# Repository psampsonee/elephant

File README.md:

# Elephant

This project is intended to be a low-power audio player for a stuffed animal. The goal is to make a box that goes into a stuffed animal that takes up minimal space and lasts as long as possible on a single battery. The box should make an animal noise when its shaken, but only after some time has elapsed since the last time it has made a noise. The noise should be audible in a quiet room and should be immediately recognizable as a particular animal - in this case, an elephant. When the box has just been shaken, it will count - with very little power - a certain amount of time, then after that, wait to be shaken. Then, if you don't shake it, it should sit there, sipping very little power. When you do, it should make the animal noise within some amount of time (maybe a few fractions of a second).

## Power Budget / Battery Life

The board will have three main power states, corresponding to the three states of the state machine:

- Low-power
    - In this state, the STM32 is in standby mode. Everything but the backup domain - that is, the RTC and the backup registers - is powered off. Due to the quiescent currents of various devices during this state, it is expected that a little under 1 uA of current will draw from the main batteries.
- Buck Converter Off
    - The STM32 backup domain is powered only from its VBAT pin by the CR-2032 coin cell. Only the RTC and the backup registers are powered. This allows the STM32 to retain an accurate representation of the time. This will draw up to 2 uA from the CR-2032. However, testing will need to be done to verify this current consumption with the RTC in its particular configuration.
    - In this state, the buck converter becomes the predominate power sink for the main batteries, drawing 1 uA of current while shut down.
- Play Sound (highest power)
    - The microcontroller and DAC/amplifier (SSM2518) are both active, and the SSM2518 draws most of the current. This state will last for a few seconds, but contributes to a significant amount of the energy consumption of the main batteries. The LT-8640 will be supplying roughly 3.7W in this state and drawing 0.41A from the battery.

## State Machine

This firmware uses the Gang-of-Four State pattern: Elephant is the Context and each concrete state implements enter/toggle/exit. Each state is exposed via a singleton instance (no per-state heap allocations); any per-device data lives in the Elephant object. Interrupt service routines are kept tiny — they set flags or enqueue events — and the main loop/state handlers process those events and perform transitions, ensuring deterministic, non-blocking behavior. See notes in the README about concurrency (brief critical sections) and buffer sizing (samples vs bytes) (TODO).

The states in the state machine will correspond to each of the states mentioned in the **Power Budget / Battery Life** section above, with the following transition causes and tasks:

- Light Sleep
    - Upon waking up from standby, the firmware will detect why was reset (confirm entering standby), and why it woke (confirm RTC alarm) in main(). Once the STM32 is in this state, the STM32 will be in standby mode, corresponding to the "Low-power" power state.
    - Transitions to Deep Sleep when real time clock alarm fires. When the alarm fires, the STM32 briefly powers on completely to do the transition. During this transition, the microcontroller must save any data that needs to be retained (probably: last sound played (avoid repetition) and any state information needing to be retained) to spare backup registers, then pull the *GPIO_pwr_buck_off* pin low, triggering the 74AUP1G74 to clear, tying the LT8640 EN/UV pin low and causing it to power down.
- Deep Sleep
    - This state never sees a transition to another state in the code as the STM32 is completely powered off during it. Instead, the transition from this state occurs when the STM32 powers back on due to the LT8640 restoring power to the board. Corresponds to **Buck Converter Off**
    - "Transitions" to Play Sound when the tilt switch pulls the preload pin of the 74AUP1G74 low briefly, pulling Q high and turning the LT8640 back on.
- Play Sound
    - Upon powering on, the firmware will detect why was reset (POR), and why it woke (power restored) in main().  In this state, the STM32 will prepare the EEPROM for reading, then load data from the EEPROM in packets while playing a sound through the Audio object. Corresponds to the power state of the same name.
    - Transitions to Light Sleep when the Audio object completes playing a sound. During this transition, the STM32 sets an alarm 4 hours ahead of the current time to trigger it to wake up and transition into deep sleep.

## Choice of Components

### LT8640 Buck Converter

The LT8640 was chosen due to its high efficiency and ability to be turned off via the enable pin, which takes very little current to drive and allows the battery to be **practically** disconnected from the circuit (x nA is expected to leak while the LT8640 is turned off).

### STM32F401CCU Microcontroller

- Powerful enough to play intelligible audio
- Low-power options allow for RTC battery backup and external wakeups
- Nearly the same chip as on a "Black Pill" (For development)

### M95M04 EEPROM

- 4 Mbit is enough for several audio files (show calcs)
- Low Power
- 200 year data retention - not an SD card

### SSM2518 I2S DAC and amplifier

- Low quiescent current
- A one-chip solution to audio (maybe I dont need to say this in the final readme)
- Powerful enough to be heard at 2W per channel
-Very low noise

### LM66100 ideal diodes (power source OR-ing)

- Low quiescent (0.3uA) and leakage (max 600nA at operating temperature) currents
- Actively controlled PFET limits reverse-current to nanoamps. This is especially important for the coin cell to avoid damage, especially in high-temperature environments where a BAT54 could cause a failure in low-power mode.
- LM66100 ideal diodes were selected for power-source OR-ing due to their low quiescent current and low reverse leakage; reverse-current behavior into the coin cell is still being validated in simulation.

## Next Steps

## Risks and Unknowns

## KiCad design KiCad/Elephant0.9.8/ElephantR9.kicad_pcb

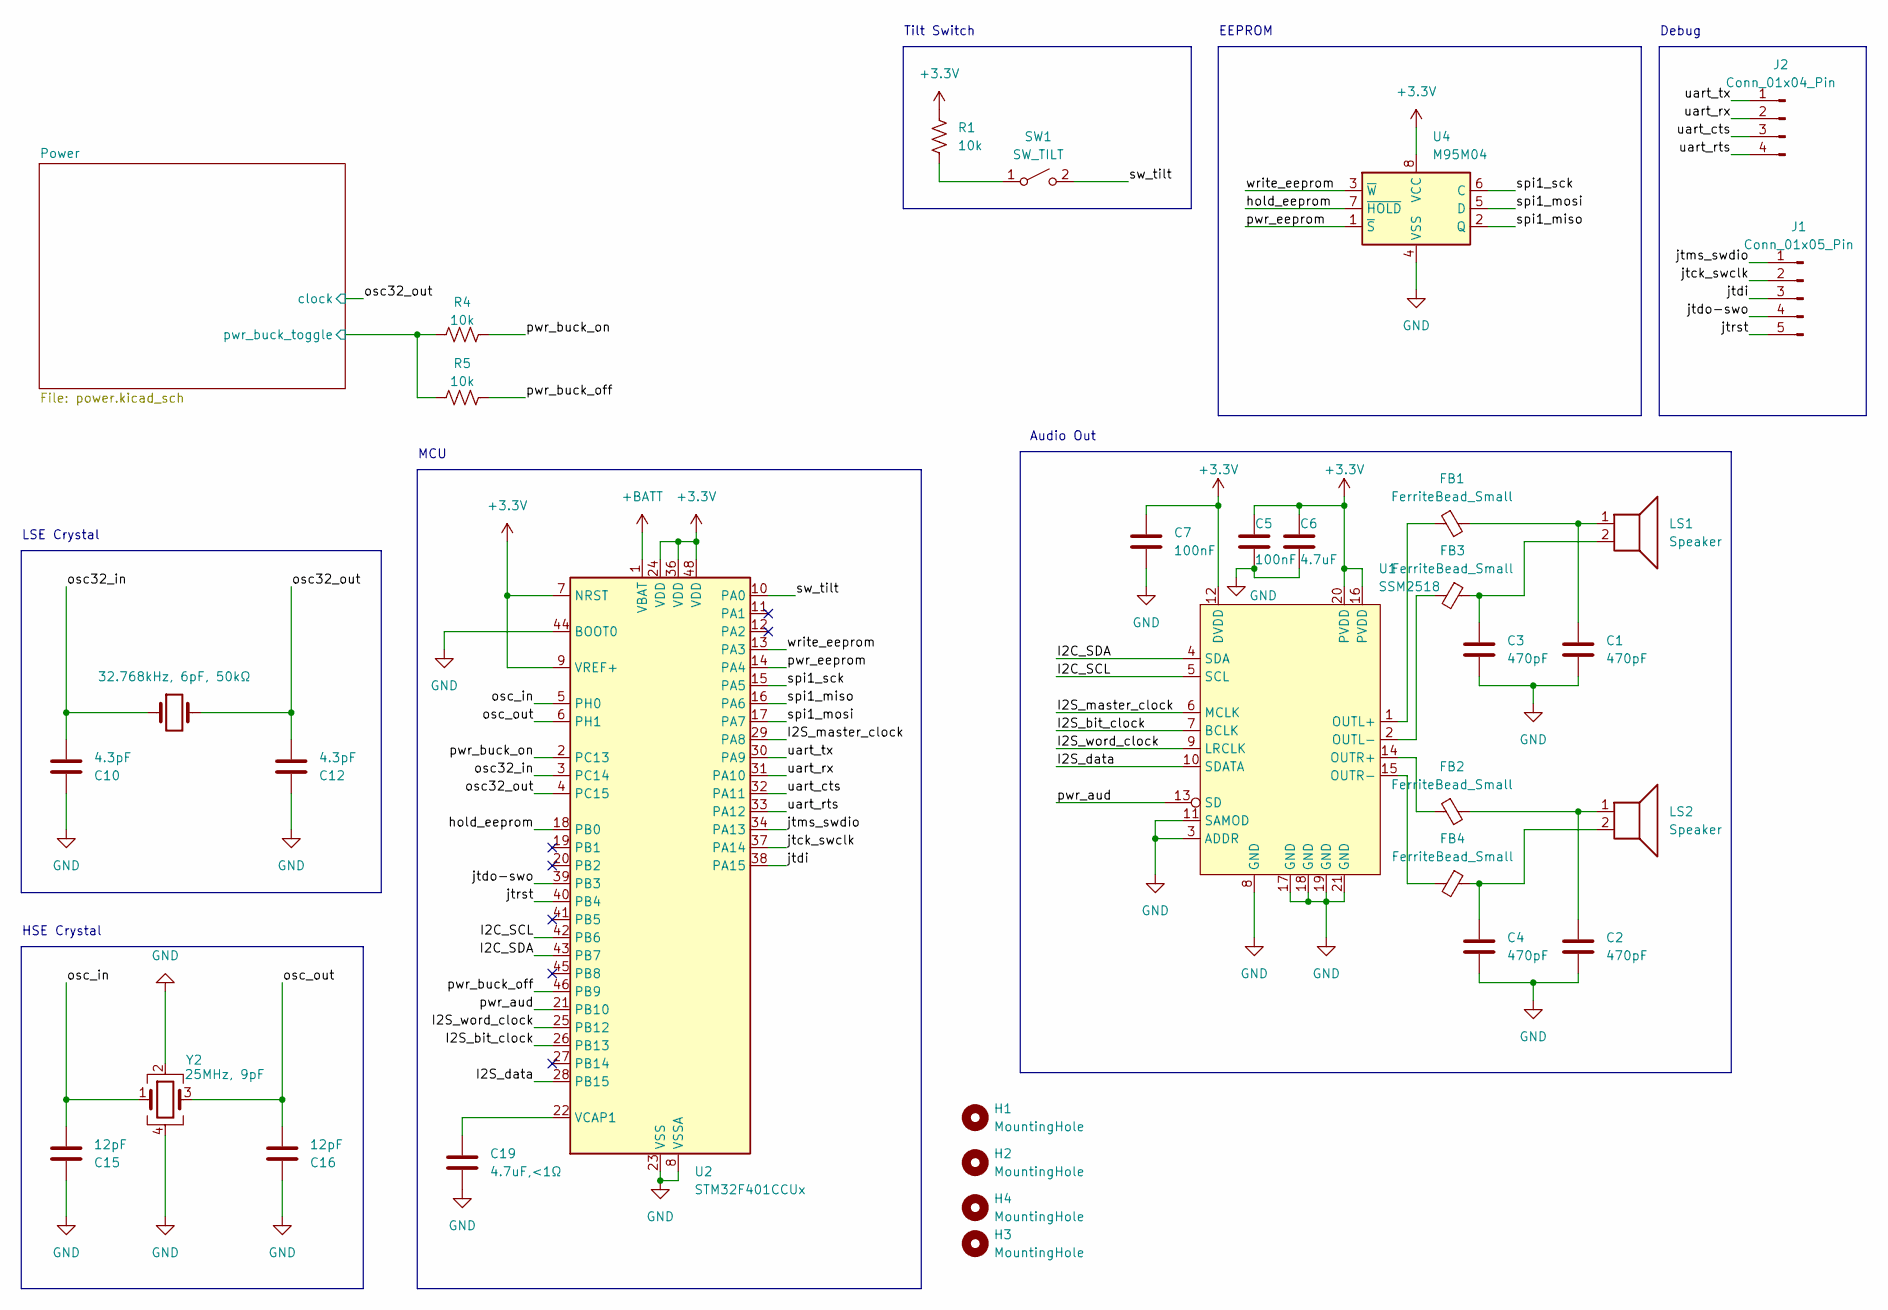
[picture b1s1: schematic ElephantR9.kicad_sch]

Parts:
C1, C2, C3, C4: 470pF; C_0603_1608Metric
C5, C7: 100nF; C_0603_1608Metric
C6: 4.7uF; C_0603_1608Metric
C10, C12: 4.3pF; C_0402_1005Metric
C15, C16: 12pF; C_0402_1005Metric
C19: 4.7uF,<1Ω; CP_Elec_4x5.4
FB1, FB2, FB3, FB4: FerriteBead_Small; L_0402_1005Metric
H1, H2, H3, H4: MountingHole; MountingHole_2.7mm_M2.5
J1: Conn_01x05_Pin; JST_PH_B5B-PH-K_1x05_P2.00mm_Vertical
J2: Conn_01x04_Pin; JST_PH_B4B-PH-K_1x04_P2.00mm_Vertical
LS1, LS2: Speaker; JST_PH_B2B-PH-K_1x02_P2.00mm_Vertical
R1, R4, R5: 10k; R_0603_1608Metric
SW1: SW_TILT; PinHeader_1x02_P2.54mm_Vertical
U1: SSM2518; QFN-20-1EP_4x4mm_P0.5mm_EP2.5x2.5mm
U2: STM32F401CCUx; QFN-48-1EP_7x7mm_P0.5mm_EP5.6x5.6mm
U4: M95M04; TSSOP-8_4.4x3mm_P0.65mm
Y1: 32.768kHz, 6pF, 50kΩ; Crystal_SMD_3215-2Pin_3.2x1.5mm
Y2: 25MHz, 9pF; Crystal_SMD_3225-4Pin_3.2x2.5mm

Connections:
+3.3V: C5.1, C6.1, C7.1, R1.1, U1.12 (DVDD), U1.16 (PVDD), U1.20 (PVDD), U2.7 (NRST), U2.9 (VREF+), U2.24 (VDD), U2.36 (VDD), U2.48 (VDD), U4.8 (VCC); also elsewhere on the board
+BATT: U2.1 (VBAT); also elsewhere on the board
/I2C_SCL: U1.5 (SCL), U2.42 (PB6)
/I2C_SDA: U1.4 (SDA), U2.43 (PB7)
/I2S_bit_clock: U1.7 (BCLK), U2.26 (PB13)
/I2S_data: U1.10 (SDATA), U2.28 (PB15)
/I2S_master_clock: U1.6 (MCLK), U2.29 (PA8)
/I2S_word_clock: U1.9 (LRCLK), U2.25 (PB12)
/Power/pwr_buck_toggle: R4.2, R5.2; also elsewhere on the board
/hold_eeprom: U2.18 (PB0), U4.7 (~HOLD)
/jtck_swclk: J1.2, U2.37 (PA14)
/jtdi: J1.3, U2.38 (PA15)
/jtdo-swo: J1.4, U2.39 (PB3)
/jtms_swdio: J1.1, U2.34 (PA13)
/jtrst: J1.5, U2.40 (PB4)
/osc32_in: C10.2, U2.3 (PC14), Y1.1
/osc32_out: C12.2, U2.4 (PC15), Y1.2; also elsewhere on the board
/osc_in: C15.2, U2.5 (PH0), Y2.1
/osc_out: C16.2, U2.6 (PH1), Y2.3
/pwr_aud: U1.13 (SD), U2.21 (PB10)
/pwr_buck_off: R5.1, U2.46 (PB9)
/pwr_buck_on: R4.1, U2.2 (PC13)
/pwr_eeprom: U2.14 (PA4), U4.1 (~S)
/spi1_miso: U2.16 (PA6), U4.2 (Q)
/spi1_mosi: U2.17 (PA7), U4.5 (D)
/spi1_sck: U2.15 (PA5), U4.6 (C)
/sw_tilt: SW1.2 (B), U2.10 (PA0)
/uart_cts: J2.3, U2.32 (PA11)
/uart_rts: J2.4, U2.33 (PA12)
/uart_rx: J2.2, U2.31 (PA10)
/uart_tx: J2.1, U2.30 (PA9)
/write_eeprom: U2.13 (PA3), U4.3 (~W)
GND: C1.2, C2.2, C3.2, C4.2, C5.2, C6.2, C7.2, C10.1, C12.1, C15.1, C16.1, C19.2, U1.3 (ADDR), U1.8 (GND), U1.11 (SAMOD), U1.17 (GND), U1.18 (GND), U1.19 (GND), U1.21 (GND), U2.8 (VSSA), U2.23 (VSS), U2.35 (VSS), U2.44 (BOOT0), U2.47 (VSS), U2.49 (VSS), U4.4 (VSS), Y2.2, Y2.4; also elsewhere on the board
unnamed: C1.1, FB1.2, LS1.1
unnamed: C2.1, FB2.2, LS2.1
unnamed: C3.1, FB3.1, LS1.2
unnamed: C4.1, FB4.1, LS2.2
unnamed: R1.2, SW1.1 (A)
unnamed: FB1.1, U1.1 (OUTL+)
unnamed: FB3.2, U1.2 (OUTL-)
unnamed: FB2.1, U1.14 (OUTR+)
unnamed: FB4.2, U1.15 (OUTR-)
unnamed: C19.1, U2.22 (VCAP1)

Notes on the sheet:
HSE Crystal
MCU
Debug
Audio Out
EEPROM
Tilt Switch
LSE Crystal

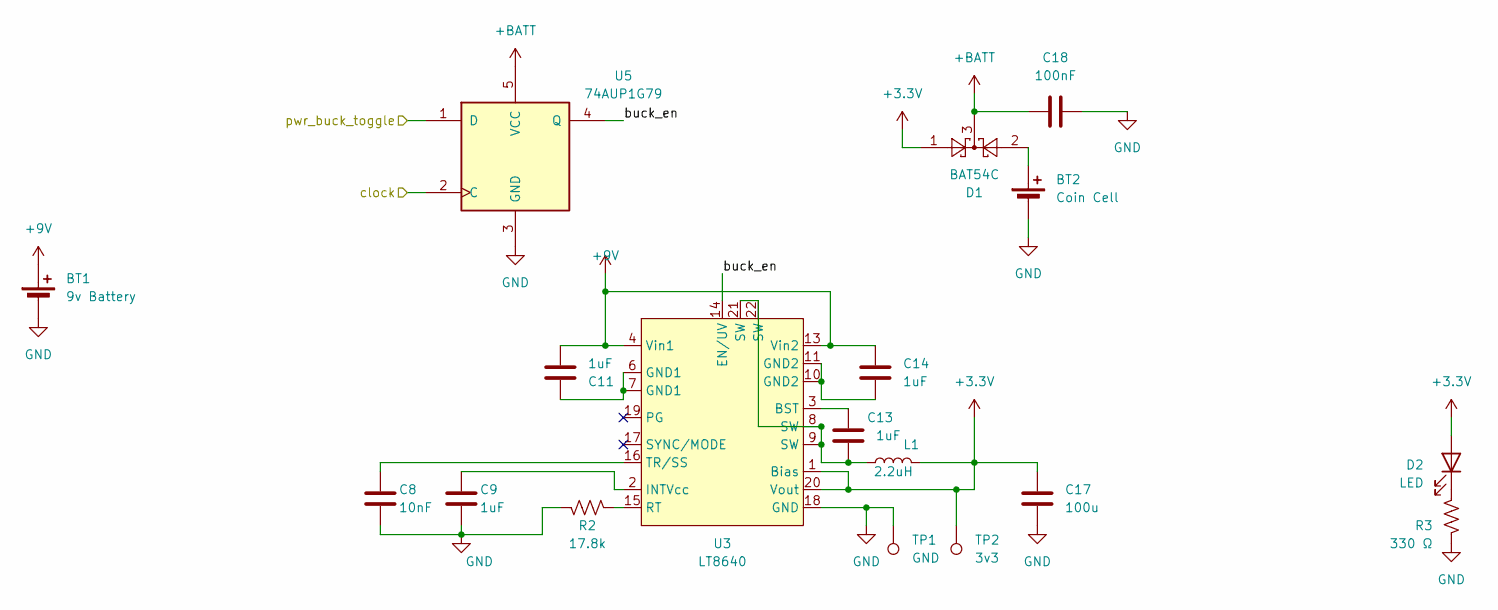
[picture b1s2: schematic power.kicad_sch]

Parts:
BT1: 9v Battery; JST_PH_B2B-PH-K_1x02_P2.00mm_Vertical
BT2: Coin Cell; BatteryHolder_Keystone_1057_1x2032
C8: 10nF; C_0603_1608Metric
C9, C11, C13, C14: 1uF; C_0603_1608Metric
C17: 100u; CP_Elec_6.3x5.3
C18: 100nF; C_0402_1005Metric
D1: BAT54C; SOT-23
D2: LED; LED_0603_1608Metric
L1: 2.2uH; L_Bourns-SRN8040_8x8.15mm
R2: 17.8k; R_0603_1608Metric
R3: 330 Ω; R_0603_1608Metric
TP1: GND; TestPoint_Pad_D1.0mm
TP2: 3v3; TestPoint_Pad_D1.0mm
U3: LT8640
U5: 74AUP1G79; SOT-23-5

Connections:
+3.3V: C17.1, D1.1, D2.2 (A), L1.2, TP2.1, U3.1 (Bias), U3.20 (Vout); also elsewhere on the board
+9V: BT1.1 (+), C11.2, C14.1, U3.4 (Vin1), U3.13 (Vin2)
+BATT: C18.1, D1.3, U5.5 (VCC); also elsewhere on the board
/Power/buck_en: U3.14 (EN/UV), U5.4 (Q)
/Power/pwr_buck_toggle: U5.1 (D); also elsewhere on the board
/osc32_out: U5.2 (C); also elsewhere on the board
GND: BT1.2 (-), BT2.2 (-), C8.2, C9.2, C17.2, C18.2, R2.2, R3.2, TP1.1, U3.18 (GND), U5.3 (GND); also elsewhere on the board
unnamed: BT2.1 (+), D1.2
unnamed: C11.1, U3.6 (GND1), U3.7 (GND1)
unnamed: C13.2, L1.1, U3.8 (SW), U3.9 (SW), U3.21 (SW), U3.22 (SW)
unnamed: C14.2, U3.10 (GND2), U3.11 (GND2)
unnamed: D2.1 (K), R3.1
unnamed: C13.1, U3.3 (BST)
unnamed: C9.1, U3.2 (INTVcc)
unnamed: R2.1, U3.15 (RT)
unnamed: C8.1, U3.16 (TR/SS)

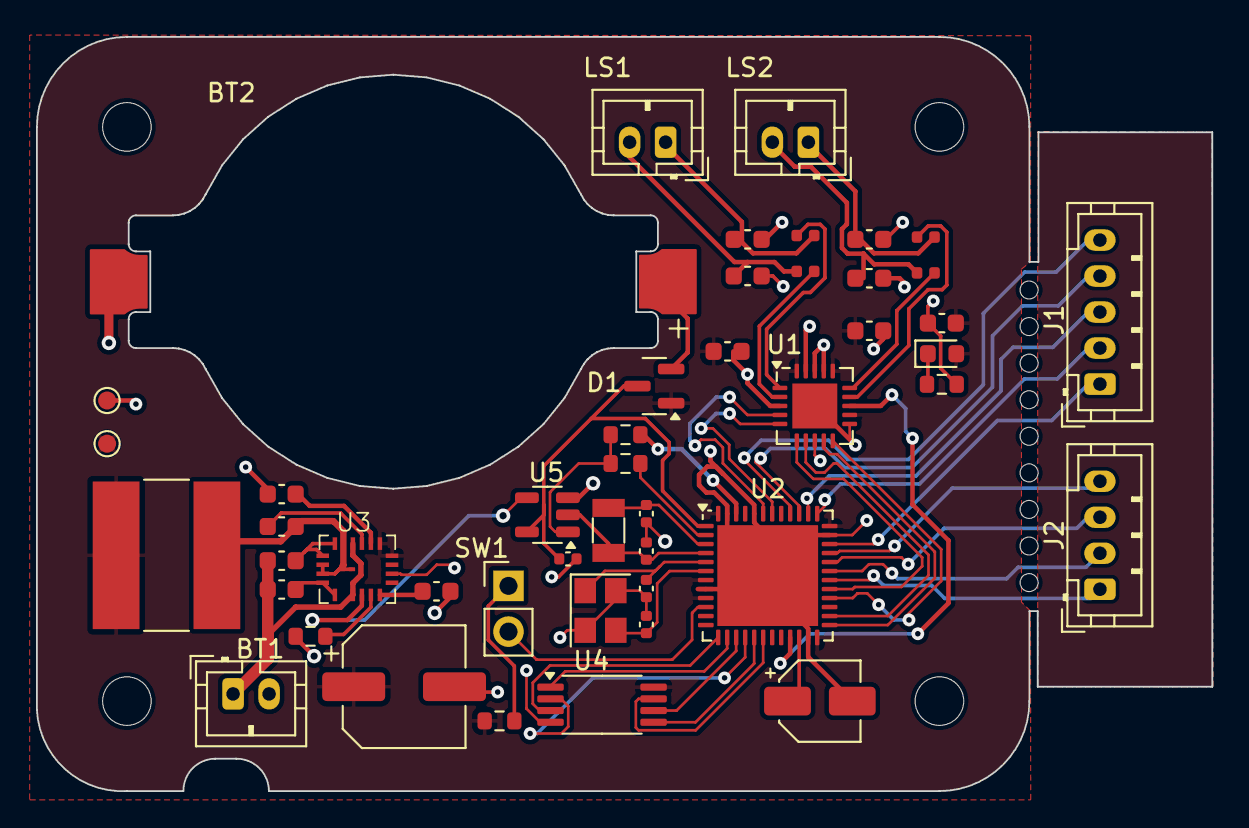
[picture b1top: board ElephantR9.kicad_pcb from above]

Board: 2 copper layers, 65.3 x 41.9 mm, 51 parts (0 on the bottom side), 54 nets.

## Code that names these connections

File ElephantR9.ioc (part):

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Mcu.Name=STM32F401C(B-C)Ux
Mcu.Package=UFQFPN48
Mcu.UserName=STM32F401CCUx
PA0-WKUP.GPIOParameters=GPIO_Label
PA0-WKUP.GPIO_Label=sw_tilt
PA0-WKUP.Mode=SYS_WakeUp0
PA0-WKUP.Signal=SYS_WKUP
PA1.GPIOParameters=GPIO_Label
PA1.GPIO_Label=ld_heartbeat
PA1.Signal=GPIO_Output
PA10.Mode=Asynchronous
PA10.Signal=USART1_RX
PA11.Mode=CTS_RTS
PA11.Signal=USART1_CTS
PA12.Mode=CTS_RTS
PA12.Signal=USART1_RTS
PA13.Mode=JTAG_5_pins
PA13.Signal=SYS_JTMS-SWDIO
PA14.Mode=JTAG_5_pins
PA14.Signal=SYS_JTCK-SWCLK
PA15.Mode=JTAG_5_pins
PA15.Signal=SYS_JTDI
PA2.GPIOParameters=GPIO_PuPd,GPIO_Label,GPIO_ModeDefaultEXTI
PA2.GPIO_Label=wakeup
PA2.GPIO_ModeDefaultEXTI=GPIO_MODE_IT_FALLING
PA2.GPIO_PuPd=GPIO_PULLUP
PA2.Signal=GPXTI2
PA3.GPIOParameters=GPIO_Label
PA3.GPIO_Label=pwr_eeprom
PA3.Signal=GPIO_Output
PA4.GPIOParameters=GPIO_Label
PA4.GPIO_Label=write_eeprom
PA4.Signal=GPIO_Output
PA5.Mode=Full_Duplex_Master
PA5.Signal=SPI1_SCK
PA6.Mode=Full_Duplex_Master
PA6.Signal=SPI1_MISO
PA7.Mode=Full_Duplex_Master
PA7.Signal=SPI1_MOSI
PA8.Mode=Clock-out-1
PA8.Signal=RCC_MCO_1
PA9.Mode=Asynchronous
PA9.Signal=USART1_TX
PB0.GPIOParameters=GPIO_Label
PB0.GPIO_Label=hold_eeprom
PB0.Signal=GPIO_Output
PB10.GPIOParameters=GPIO_Label
PB10.GPIO_Label=pwr_aud
PB10.Signal=GPIO_Output
PB12.Mode=Half_Duplex_Master
PB12.Signal=I2S2_WS
PB13.Mode=Half_Duplex_Master
PB13.Signal=I2S2_CK
PB15.Mode=Half_Duplex_Master
PB15.Signal=I2S2_SD
PB3.Mode=JTAG_5_pins
PB3.Signal=SYS_JTDO-SWO
PB4.Mode=JTAG_5_pins
PB4.Signal=SYS_JTRST
PB6.Mode=I2C
PB6.Signal=I2C1_SCL
PB7.Mode=I2C
PB7.Signal=I2C1_SDA
PC13-ANTI_TAMP.Mode=AlarmA_RoutedAF
PC13-ANTI_TAMP.Signal=RTC_AF1
PC14-OSC32_IN.Mode=LSE-External-Oscillator
PC14-OSC32_IN.Signal=RCC_OSC32_IN
PC15-OSC32_OUT.Mode=LSE-External-Oscillator
PC15-OSC32_OUT.Signal=RCC_OSC32_OUT
PH0\ -\ OSC_IN.Mode=HSE-External-Oscillator
PH0\ -\ OSC_IN.Signal=RCC_OSC_IN
PH1\ -\ OSC_OUT.Mode=HSE-External-Oscillator
PH1\ -\ OSC_OUT.Signal=RCC_OSC_OUT
RCC.HSE_VALUE=25000000
RCC.SYSCLKFreq_VALUE=84000000
RCC.SYSCLKSource=RCC_SYSCLKSOURCE_PLLCLK
board=custom

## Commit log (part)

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2026-02-01 Created TODO, JOURNAL
2026-02-01 Pushing recent changes.
2026-05-31 Added KiCad project files, LTSpice files, and documentation files.
2026-06-06 Restore manual STM32 build flash debug workflow
2026-06-10 Reading SD Card
    SD card to be used for temporary storage for audio-test
2026-06-28 Audio player software design started.
